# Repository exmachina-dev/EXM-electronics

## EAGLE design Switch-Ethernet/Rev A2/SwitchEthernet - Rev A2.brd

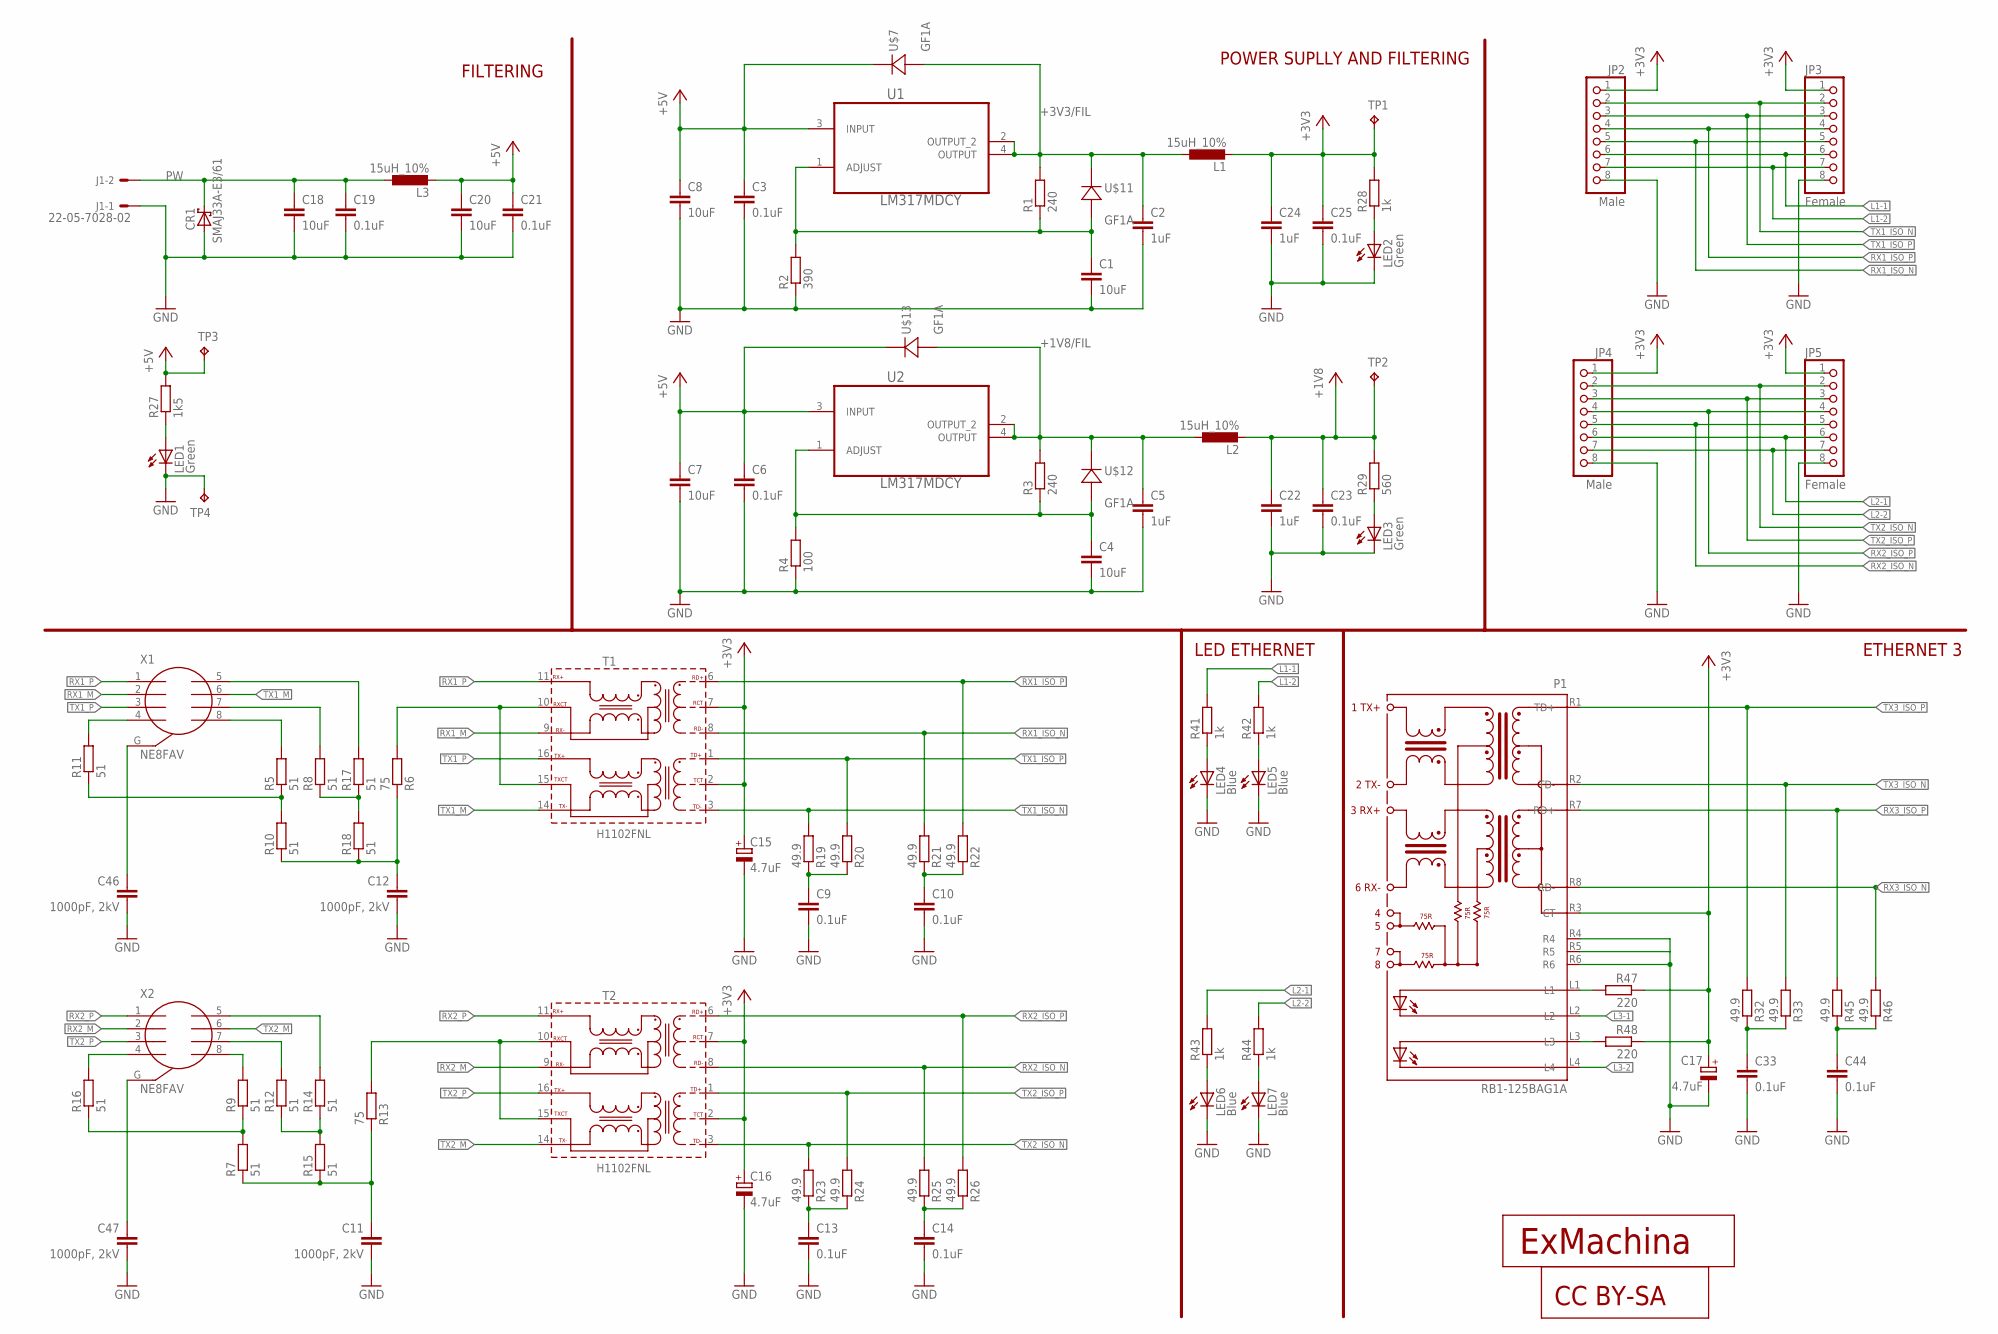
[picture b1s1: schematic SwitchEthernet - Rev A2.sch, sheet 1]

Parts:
C1, C4, C7, C8, C18, C20: 10uF; C0603; MPN MCNP16V106M5X11
C2, C5, C22, C24: 1uF; C0603; MPN MC0603B105K160CT
C3, C6, C9, C10, C13, C14, C19, C21, C23, C25, C33, C44: 0.1uF; C0603; MPN MC0603B104K160CT
C11, C12, C46, C47: 1000pF, 2kV; C1206; MPN MC1206B102K202CT
C15, C16, C17: 4.7uF; CT3216; MPN MCCTA475M010
CR1: SMAJ33A-E3/61; DIODE_DO-214AC; MPN SMAJ33A-E3/61
J1: 22-05-7028-02; 7395-02; MPN 22-05-7028
JP2, JP4: Male; 1X08; MPN 2211S-08G
JP3, JP5: Female; 1X08; MPN 2212S-08SG-85
L1, L2, L3: 15uH_10%; L4532M; MPN LQH43CN150K03L
LED1, LED2, LED3: Green; CHIP-LED0603; MPN OVS-0604
LED4, LED5, LED6, LED7: Blue; CHIP-LED0603; MPN OVS-0603
P1: RB1-125BAG1A; WIZNET_RB1-125BAG1A
R1, R3: 240; R0603; MPN MC0063W06031240R
R2: 390; R0603; MPN MC0063W06031390R
R4: 100; R0603; MPN MC0063W06031100R
R5, R7, R8, R9, R10, R11, R12, R14, R15, R16, R17, R18: 51; R0603; MPN MC0063W0603151R
R6, R13: 75; R0603; MPN MC0063W0603175R
R19, R20, R21, R22, R23, R24, R25, R26, R32, R33, R45, R46: 49.9; R0603; MPN MC0603SAF499JT5E
R27: 1k5; R0603; MPN MC0063W060311K5
R28, R41, R42, R43, R44: 1k; R0603; MPN MCMR06X1001FTL
R29: 560; R0603; MPN MCMR06X1501FTL
R47, R48: 220; R0603; MPN MC0063W06031220R
T1, T2: H1102FNL; HXXXX
TP1, TP2, TP3, TP4: TPB1,27; B1,27
U1, U2: LM317MDCY; SOT230P700X180-4N
U$5: EXMACHINA-LOGO-NAME; EXM-LOGO-BASELINE
U$6: CC-BY-SA
U$7, U$11, U$12, U$13: GF1A; DO-214BA; MPN GF1B-E3/67A
X1, X2: NE8FAV

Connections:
+1V8: C22.1, C23.1, L2.2, R29.2, TP2.TP; also elsewhere on the board
+1V8/FIL: C5.1, L2.1, R3.2, U2.2 (OUTPUT_2), U2.4 (OUTPUT), U$12.C (1), U$13.A (2)
+3V3: C15.+, C16.+, C17.+, C24.1, C25.1, JP2.1, JP3.1, JP4.1, JP5.1, L1.2, P1.R3 (CT), R28.2, R47.1, R48.1, T1.2 (TCT), T1.7 (RCT), T2.2 (TCT), T2.7 (RCT), TP1.TP; also elsewhere on the board
+3V3/FIL: C2.1, L1.1, R1.2, U1.2 (OUTPUT_2), U1.4 (OUTPUT), U$7.A (2), U$11.C (1)
+5V: C3.1, C6.1, C7.1, C8.1, C20.1, C21.1, L3.2, R27.2, TP3.TP, U1.3 (INPUT), U2.3 (INPUT), U$7.C (1), U$13.C (1)
GND: C1.2, C2.2, C3.2, C4.2, C5.2, C6.2, C7.2, C8.2, C9.2, C10.2, C11.2, C12.2, C13.2, C14.2, C15.-, C16.-, C17.-, C18.2, C19.2, C20.2, C21.2, C22.2, C23.2, C24.2, C25.2, C33.2, C44.2, C46.2, C47.2, CR1.2 (A), J1.1, JP2.8, JP3.8, JP4.8, JP5.8, LED1.C, LED2.C, LED3.C, LED4.C, LED5.C, LED6.C, LED7.C, P1.R4, P1.R5, P1.R6, R2.1, R4.1, TP4.TP; also elsewhere on the board
L1-1: JP2.6, JP3.6, R41.2; also elsewhere on the board
L1-2: JP2.7, JP3.7, R42.2; also elsewhere on the board
L2-1: JP4.6, JP5.6, R43.2; also elsewhere on the board
L2-2: JP4.7, JP5.7, R44.2; also elsewhere on the board
L3-1: P1.L2; also elsewhere on the board
L3-2: P1.L4; also elsewhere on the board
unnamed: R6.2, T1.10 (RXCT), T1.15 (TXCT)
unnamed: C1.1, R1.1, R2.2, U1.1 (ADJUST), U$11.A (2)
unnamed: R13.2, T2.10 (RXCT), T2.15 (TXCT)
unnamed: R9.2, X2.8
unnamed: C4.1, R3.1, R4.2, U2.1 (ADJUST), U$12.A (2)
unnamed: R11.2, X1.4
unnamed: R5.2, X1.8
unnamed: R8.2, X1.7
unnamed: C9.1, R19.1, R20.1
unnamed: R17.2, X1.5
unnamed: R12.2, X2.7
unnamed: C11.1, R7.1, R13.1, R15.1
unnamed: R5.1, R10.2, R11.1
unnamed: R16.2, X2.4
unnamed: R7.2, R9.1, R16.1
unnamed: R8.1, R17.1, R18.2
unnamed: R14.2, X2.5
unnamed: R12.1, R14.1, R15.2
unnamed: LED4.A, R41.1
unnamed: LED1.A, R27.1
unnamed: LED2.A, R28.1
unnamed: LED3.A, R29.1
unnamed: C33.1, R32.1, R33.1
unnamed: LED5.A, R42.1
unnamed: LED6.A, R43.1
unnamed: LED7.A, R44.1
unnamed: C44.1, R45.1, R46.1
unnamed: C12.1, R6.1, R10.1, R18.1
unnamed: C10.1, R21.1, R22.1
unnamed: P1.L3, R48.2
unnamed: P1.L1, R47.2
unnamed: C47.1, X2.G
unnamed: C46.1, X1.G
unnamed: C13.1, R23.1, R24.1
unnamed: C14.1, R25.1, R26.1
PW: C18.1, C19.1, CR1.1 (C), J1.2, L3.1
RX1_ISO_N: JP2.5, JP3.5, R21.2, T1.8 (RD-); also elsewhere on the board
RX1_ISO_P: JP2.4, JP3.4, R22.2, T1.6 (RD+); also elsewhere on the board
RX1_M: T1.9 (RX-), X1.2
RX1_P: T1.11 (RX+), X1.1
RX2_ISO_N: JP4.5, JP5.5, R25.2, T2.8 (RD-); also elsewhere on the board
RX2_ISO_P: JP4.4, JP5.4, R26.2, T2.6 (RD+); also elsewhere on the board
RX2_M: T2.9 (RX-), X2.2
RX2_P: T2.11 (RX+), X2.1
RX3_ISO_N: P1.R8 (RD-), R46.2; also elsewhere on the board
RX3_ISO_P: P1.R7 (RD+), R45.2; also elsewhere on the board
TX1_ISO_N: JP2.2, JP3.2, R19.2, T1.3 (TD-); also elsewhere on the board
TX1_ISO_P: JP2.3, JP3.3, R20.2, T1.1 (TD+); also elsewhere on the board
TX1_M: T1.14 (TX-), X1.6
TX1_P: T1.16 (TX+), X1.3
TX2_ISO_N: JP4.2, JP5.2, R23.2, T2.3 (TD-); also elsewhere on the board
TX2_ISO_P: JP4.3, JP5.3, R24.2, T2.1 (TD+); also elsewhere on the board
TX2_M: T2.14 (TX-), X2.6
TX2_P: T2.16 (TX+), X2.3
TX3_ISO_N: P1.R2 (TD-), R33.2; also elsewhere on the board
TX3_ISO_P: P1.R1 (TD+), R32.2; also elsewhere on the board

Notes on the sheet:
FILTERING
POWER SUPLLY AND FILTERING
LED ETHERNET
ETHERNET 3

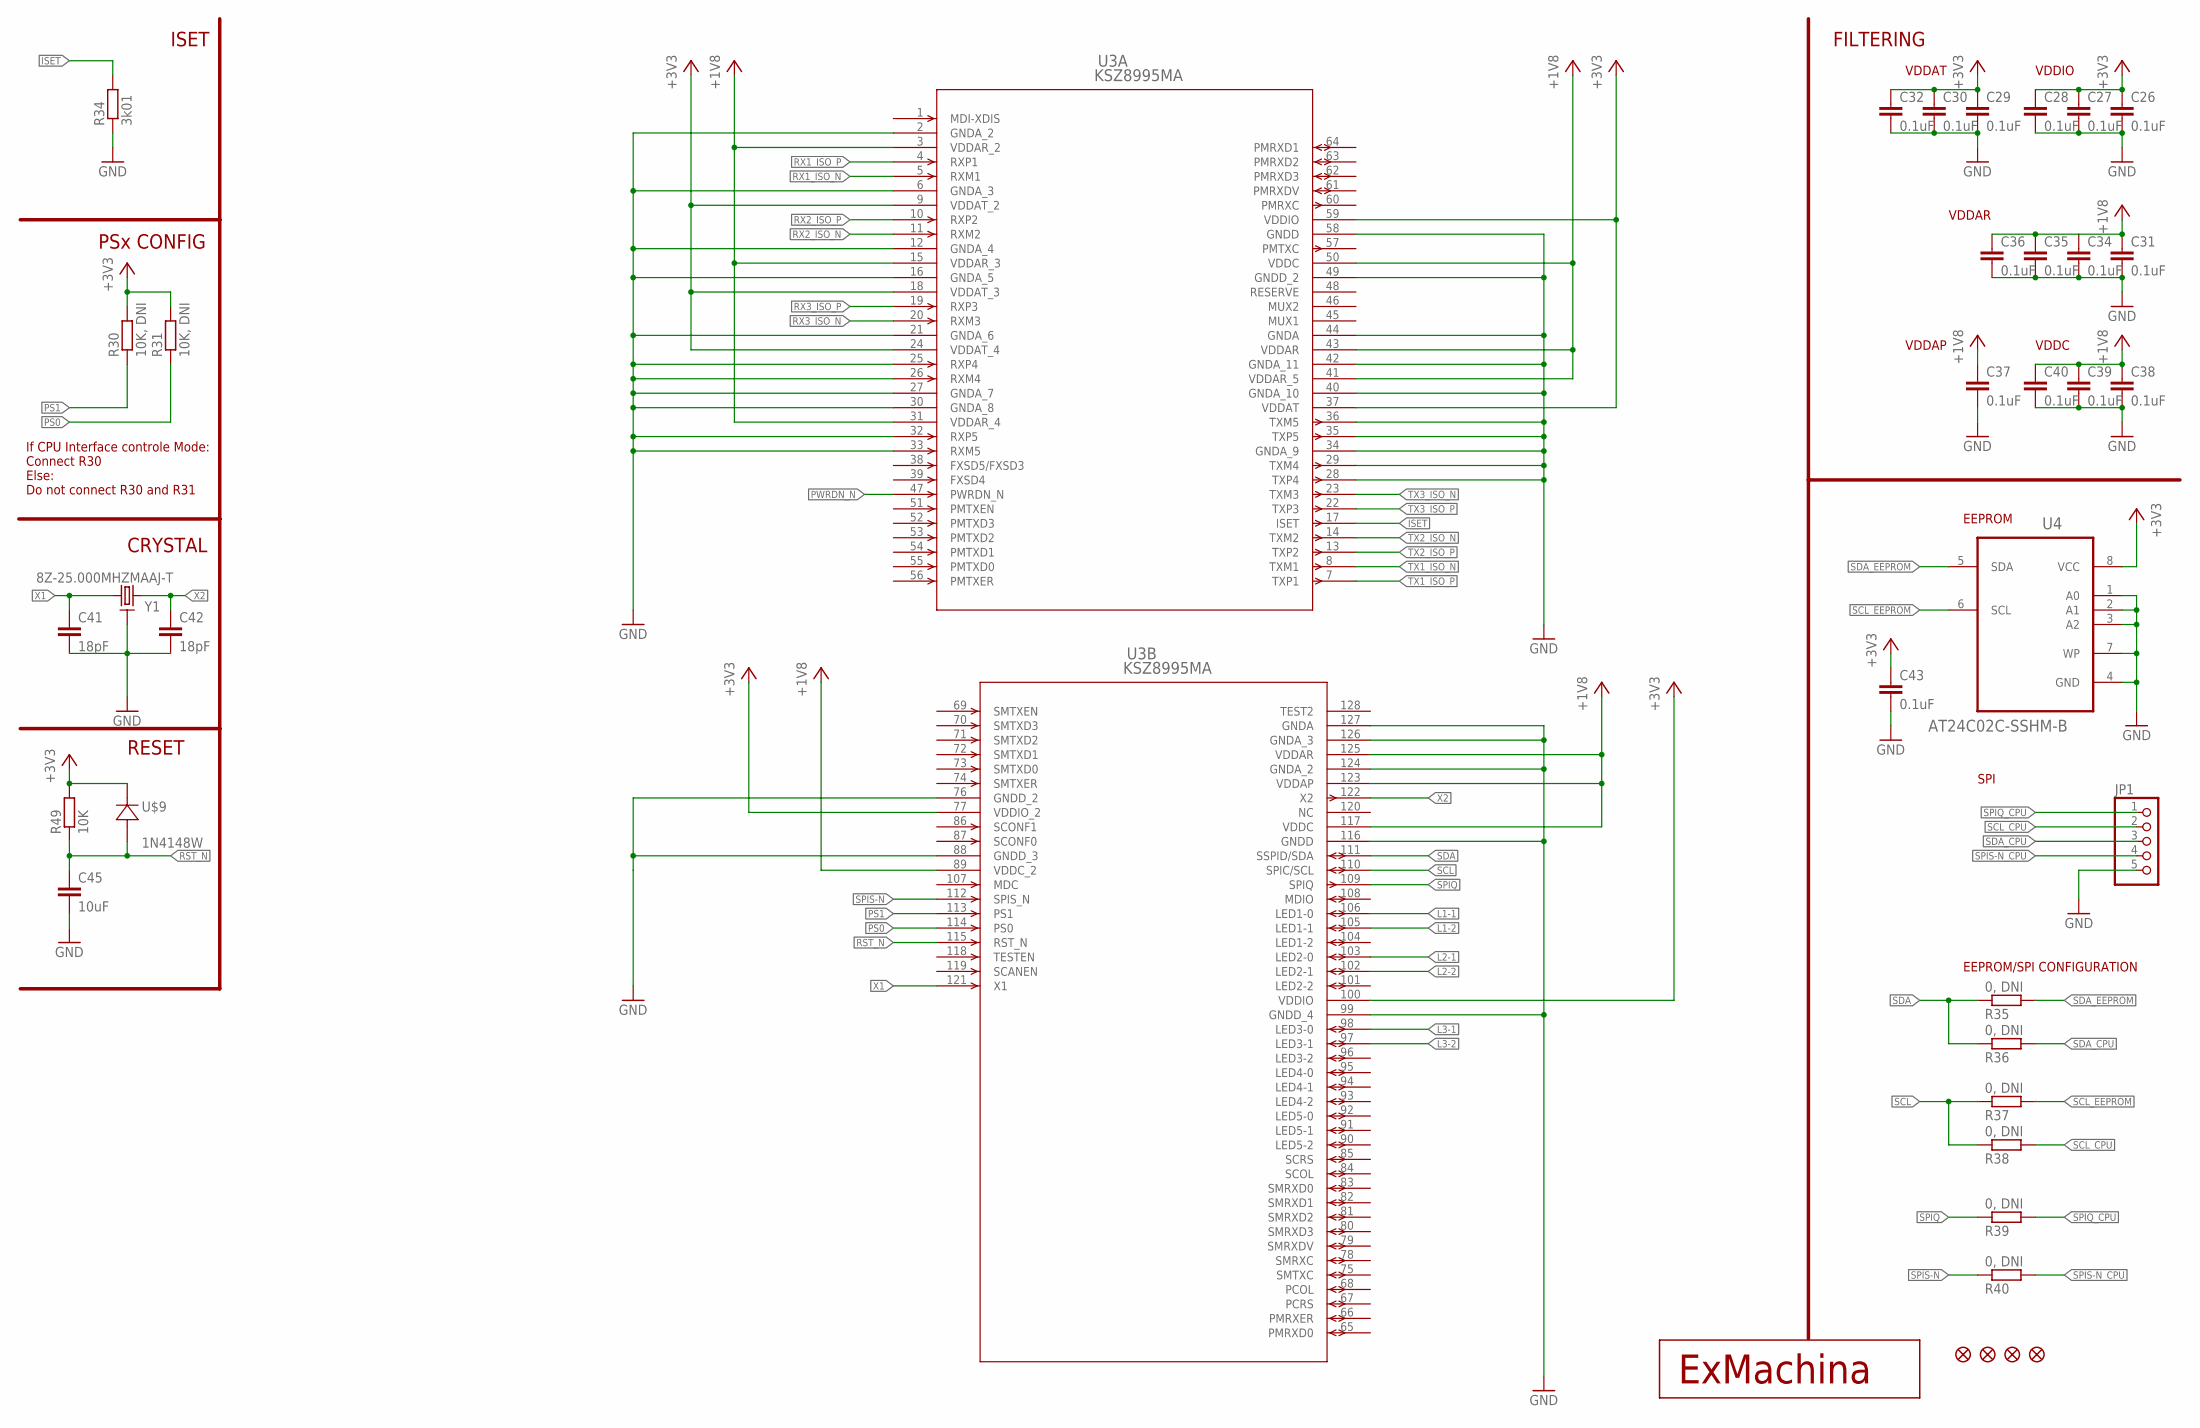
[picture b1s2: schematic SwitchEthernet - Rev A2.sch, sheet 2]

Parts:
C26, C27, C28, C29, C30, C31, C32, C34, C35, C36, C37, C38, C39, C40, C43: 0.1uF; C0603; MPN MC0603B104K160CT
C41, C42: 18pF; C0603; MPN MC0603N180J500CT
C45: 10uF; C0603; MPN MCNP16V106M5X11
JP1: PINHD-1X5; 1X05; MPN M20-9990545
JP7, JP8, JP9, JP10: FIDUCIAL1X2; FIDUCIAL-1X2
R30, R31: 10K, DNI; R0603; MPN MC0063W0603110K
R34: 3k01; R0603; MPN MC0063W060313K01
R35, R36, R37, R38, R39, R40: 0, DNI; R0603; MPN MC0603WG00000T5E-TC
R49: 10K; R0603; MPN MC0063W0603110K
U3: KSZ8995MA; PQFP-128_MQL; MPN KSZ8995MA
U4: AT24C02C-SSHM-B; SOIC127P600X175-8N
U$8: EXMACHINA-LOGO-NAME; EXM-LOGO-BASELINE
U$9: 1N4148W; SOD-123_MINI-SMA; MPN 1N4148W
Y1: 8Z-25.000MHZMAAJ-T; SMD2.5X2; MPN 8Z-25.000MAAJ-T

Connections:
+1V8: C31.1, C34.1, C35.1, C36.1, C37.1, C38.1, C39.1, C40.1, U3.3 (VDDAR_2), U3.15 (VDDAR_3), U3.31 (VDDAR_4), U3.41 (VDDAR_5), U3.43 (VDDAR), U3.50 (VDDC), U3.89 (VDDC_2), U3.117 (VDDC), U3.123 (VDDAP), U3.125 (VDDAR); also elsewhere on the board
+3V3: C26.1, C27.1, C28.1, C29.1, C30.1, C32.1, C43.1, R30.2, R31.2, R49.2, U3.9 (VDDAT_2), U3.18 (VDDAT_3), U3.24 (VDDAT_4), U3.37 (VDDAT), U3.59 (VDDIO), U3.77 (VDDIO_2), U3.100 (VDDIO), U4.8 (VCC), U$9.C (1); also elsewhere on the board
GND: C26.2, C27.2, C28.2, C29.2, C30.2, C31.2, C32.2, C34.2, C35.2, C36.2, C37.2, C38.2, C39.2, C40.2, C41.2, C42.2, C43.2, C45.2, JP1.5, R34.1, U3.2 (GNDA_2), U3.6 (GNDA_3), U3.12 (GNDA_4), U3.16 (GNDA_5), U3.21 (GNDA_6), U3.25 (RXP4), U3.26 (RXM4), U3.27 (GNDA_7), U3.28 (TXP4), U3.29 (TXM4), U3.30 (GNDA_8), U3.32 (RXP5), U3.33 (RXM5), U3.34 (GNDA_9), U3.35 (TXP5), U3.36 (TXM5), U3.40 (GNDA_10), U3.42 (GNDA_11), U3.44 (GNDA), U3.49 (GNDD_2), U3.58 (GNDD), U3.76 (GNDD_2), U3.88 (GNDD_3), U3.99 (GNDD_4), U3.116 (GNDD), U3.124 (GNDA_2), U3.126 (GNDA_3), U3.127 (GNDA), U4.1 (A0), U4.2 (A1), U4.3 (A2), U4.4 (GND), U4.7 (WP), Y1.2, Y1.4 (2); also elsewhere on the board
ISET: R34.2, U3.17 (ISET)
L1-1: U3.106 (LED1-0); also elsewhere on the board
L1-2: U3.105 (LED1-1); also elsewhere on the board
L2-1: U3.103 (LED2-0); also elsewhere on the board
L2-2: U3.102 (LED2-1); also elsewhere on the board
L3-1: U3.98 (LED3-0); also elsewhere on the board
L3-2: U3.97 (LED3-1); also elsewhere on the board
PS0: R31.1, U3.114 (PS0)
PS1: R30.1, U3.113 (PS1)
PWRDN_N: U3.47 (PWRDN_N)
RST_N: C45.1, R49.1, U3.115 (RST_N), U$9.A (2)
RX1_ISO_N: U3.5 (RXM1); also elsewhere on the board
RX1_ISO_P: U3.4 (RXP1); also elsewhere on the board
RX2_ISO_N: U3.11 (RXM2); also elsewhere on the board
RX2_ISO_P: U3.10 (RXP2); also elsewhere on the board
RX3_ISO_N: U3.20 (RXM3); also elsewhere on the board
RX3_ISO_P: U3.19 (RXP3); also elsewhere on the board
SCL: R37.1, R38.1, U3.110 (SPIC/SCL)
SCL_CPU: JP1.2, R38.2
SCL_EEPROM: R37.2, U4.6 (SCL)
SDA: R35.1, R36.1, U3.111 (SSPID/SDA)
SDA_CPU: JP1.3, R36.2
SDA_EEPROM: R35.2, U4.5 (SDA)
SPIQ: R39.1, U3.109 (SPIQ)
SPIQ_CPU: JP1.1, R39.2
SPIS-N: R40.1, U3.112 (SPIS_N)
SPIS-N_CPU: JP1.4, R40.2
TX1_ISO_N: U3.8 (TXM1); also elsewhere on the board
TX1_ISO_P: U3.7 (TXP1); also elsewhere on the board
TX2_ISO_N: U3.14 (TXM2); also elsewhere on the board
TX2_ISO_P: U3.13 (TXP2); also elsewhere on the board
TX3_ISO_N: U3.23 (TXM3); also elsewhere on the board
TX3_ISO_P: U3.22 (TXP3); also elsewhere on the board
X1: C41.1, U3.121 (X1), Y1.1
X2: C42.1, U3.122 (X2), Y1.3

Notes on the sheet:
ISET
FILTERING
VDDIO
VDDAT
VDDAR
VDDC
VDDAP
PSx CONFIG
If CPU Interface controle Mode: Connect R30 Else: Do not connect R30 and R31
CRYSTAL
EEPROM
SPI
EEPROM/SPI CONFIGURATION
RESET

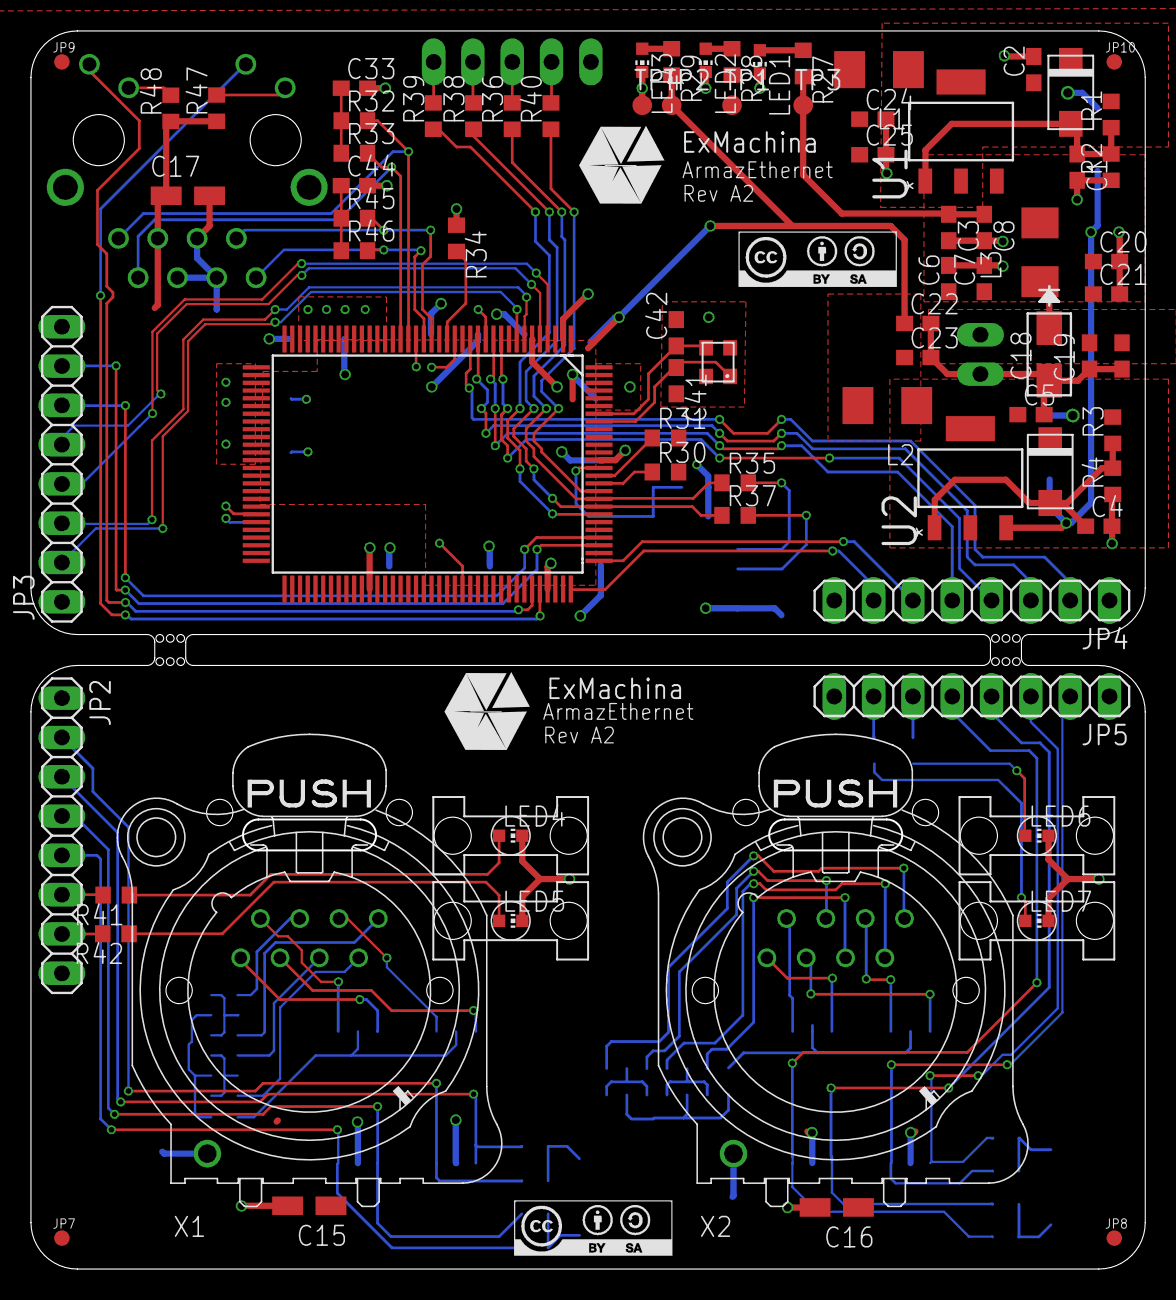
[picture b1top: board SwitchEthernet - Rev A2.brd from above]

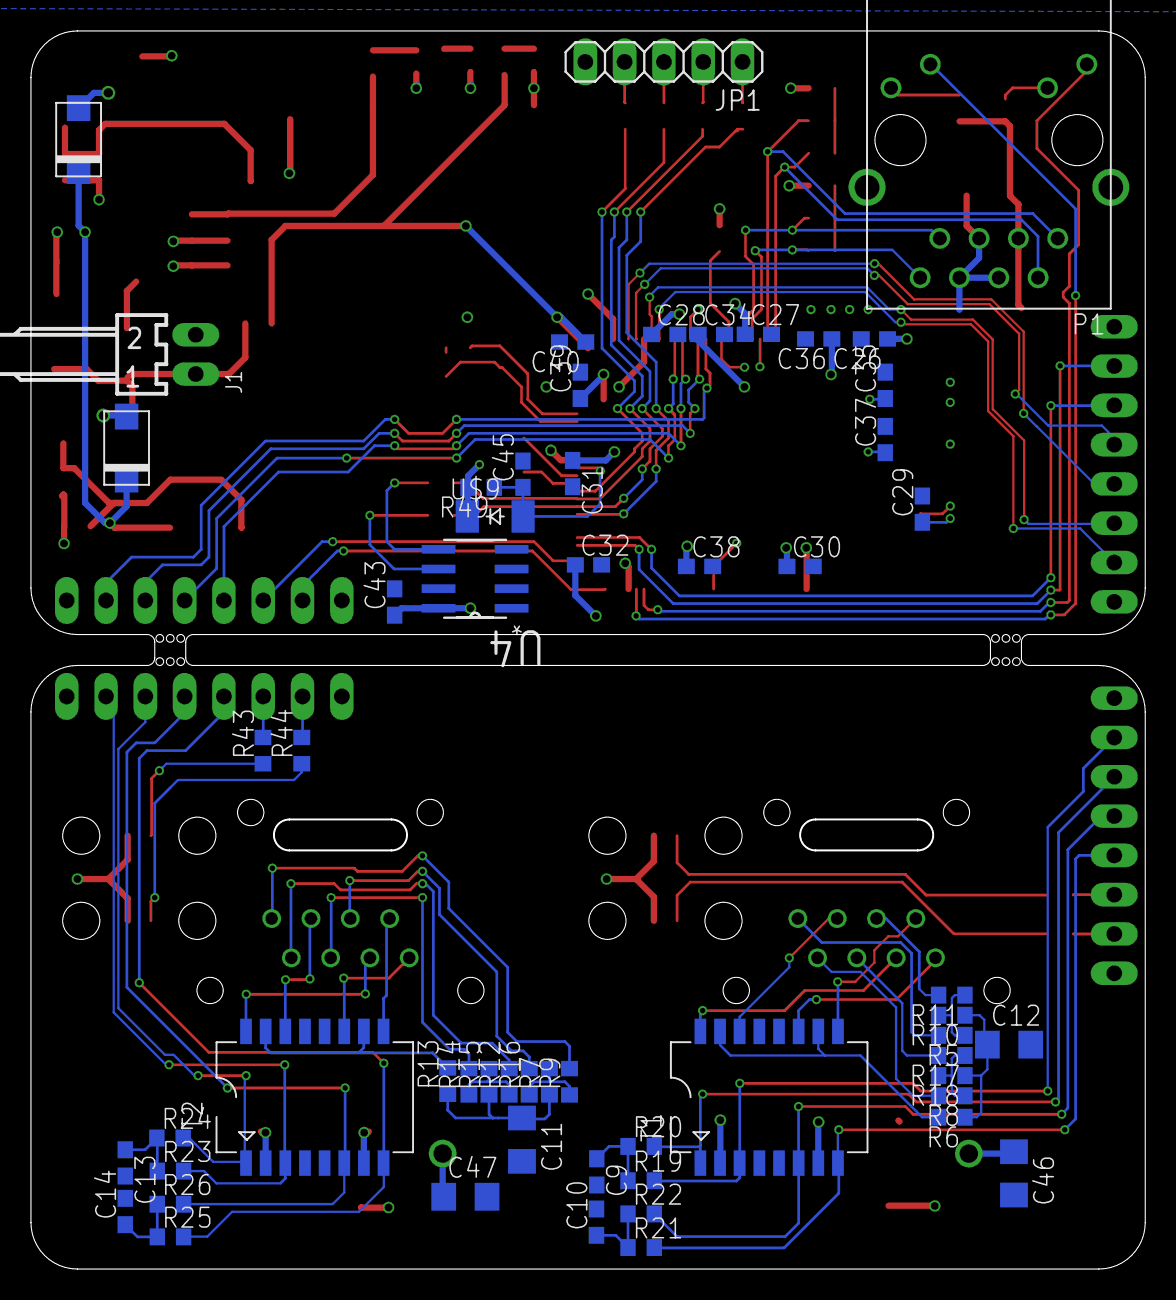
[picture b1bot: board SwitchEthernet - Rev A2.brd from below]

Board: 2 copper layers, 72.0 x 80.0 mm, 144 parts (58 on the bottom side), 84 nets.

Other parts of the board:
U$1, U$2, U$3, U$4: 1275.100
U$10: CC-BY-SA

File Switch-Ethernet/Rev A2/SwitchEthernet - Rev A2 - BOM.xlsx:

Qty | Value | Device | Package | Parts | Description COPYRIGHT | FAMILY MANUFACTURER_NAME MANUFACTURER_PART_NUMBER MF | MPN OC_FARNELL | OC_NEWARK PACKAGE RSPARTNUMBER SECTION SUPERSECTION SUPPLIER TP_SIGNAL_NAME VEN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
1 |  | PINHD-1X5 | 1X05 | JP1 | PIN HEADER |  | M20-9990545 | 97K6210
6 | 0, DNI | R-EU_R0603 | R0603 | R35, R36, R37, R38, R39, R40 | RESISTOR, European symbol | Multicomp | MC0603WG00000T5E-TC | 58K4684
27 | 0.1uF | C-EUC0603 | C0603 | C3, C6, C9, C10, C13, C14, C19, C21, C23, C25, C26, C27, C28, C29, C30, C31, C3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 | CAPACITOR, European symbol |  | MC0603B104K160CT | 06R4923
1 | 100 | R-EU_R0603 | R0603 | R4 | RESISTOR, European symbol | Multicomp | MC0063W06031100R | 58K4446
4 | 1000pF, 2kV | C-EUC1206 | C1206 | C11, C12, C46, C47 | CAPACITOR, European symbol |  | MC1206B102K202CT | 21T9879
1 | 10K | R-EU_R0603 | R0603 | R49 | RESISTOR, European symbol | Multicomp | MC0063W0603110K | 58K4450
2 | 10K, DNI | R-EU_R0603 | R0603 | R30, R31 | RESISTOR, European symbol | Multicomp | MC0063W0603110K | 58K4450
7 | 10uF | C-EUC0603 | C0603 | C1, C4, C7, C8, C18, C20, C45 | CAPACITOR, European symbol |  | MCNP16V106M5X11 | 13M5149
3 | 15uH_10% | L-EUL4532C | L4532M | L1, L2, L3 | INDUCTOR, European symbol |  | LQH43CN150K03L | 74M2809
2 | 18pF | C-EUC0603 | C0603 | C41, C42 | CAPACITOR, European symbol |  | MC0603N180J500CT | 06R5138
1 | 1N4148W | 1N4148W | SOD-123_MINI-SMA | U$9 |  |  | 1N4148W | 01P4213
5 | 1k | R-EU_R0603 | R0603 | R28, R41, R42, R43, R44 | RESISTOR, European symbol |  | MCMR06X1001FTL | 86T3505
1 | 1k5 | R-EU_R0603 | R0603 | R27 | RESISTOR, European symbol | Multicomp | MC0063W060311K5 | 58K4488
4 | 1uF | C-EUC0603 | C0603 | C2, C5, C22, C24 | CAPACITOR, European symbol |  | MC0603B105K160CT | 06X6171
1 | 22-05-7028-02 | 22-05-7028-02 | 2007041 | J1 | CONNECTOR |  | 22-05-7028 9731601 | 25M1728
2 | 220 | R-EU_R0603 | R0603 | R47, R48 | RESISTOR, European symbol | Multicomp | MC0063W06031220R | 58K4526
2 | 240 | R-EU_R0603 | R0603 | R1, R3 | RESISTOR, European symbol |  | MC0063W06031240R | 94W5763
1 | 390 | R-EU_R0603 | R0603 | R2 | RESISTOR, European symbol | Multicomp | MC0063W06031390R | 58K4586
1 | 3k01 | R-EU_R0603 | R0603 | R34 | RESISTOR, European symbol |  | MC0063W060313K01 | 94W5780
3 | 4.7uF | CPOL-EUCT3216 | CT3216 | C15, C16, C17 | POLARIZED CAPACITOR, European symbol |  | MCCTA475M010 | 01M8221
12 | 49.9 | R-EU_R0603 | R0603 | R19, R20, R21, R22, R23, R24, R25, R26, R32, R33, R45, R46 | RESISTOR, European symbol |  | MC0603SAF499JT5E | 79M5983
12 | 51 | R-EU_R0603 | R0603 | R5, R7, R8, R9, R10, R11, R12, R14, R15, R16, R17, R18 | RESISTOR, European symbol | Multicomp | MC0063W0603151R | 58K4614
1 | 560 | R-EU_R0603 | R0603 | R29 | RESISTOR, European symbol |  | MCMR06X1501FTL | 86T3542
2 | 75 | R-EU_R0603 | R0603 | R6, R13 | RESISTOR, European symbol | Multicomp | MC0063W0603175R | 58K4654
1 | 8Z-25.000MHZM | AAJ-T 8Z-25.000MHZMAAJ-T | SMD2.5X2 | Y1 |  |  | 8Z-25.000MAAJ-T | 84R5794
1 | AT24C02C-SSHM | #NAME? | SOIC127P600X175-8N | U4 | SERIAL EEPROM IC Memory Size:2Kbit,8-SOIC |  | AT24C02C-SSHM-B 1971995 | 68T4066 8SOIC ATMEL
4 | Blue | LEDCHIP-LED0603 | CHIP-LED0603 | LED4, LED5, LED6, LED7 | LED |  | OVS-0603 | 15R2205
1 | CC-BY-SA | CC-BY-SA | CC-BY-SA | U$6 |  |  |  | unknown
2 | EXMACHINA-LOG | O-NAME EXMACHINA-LOGO-NAME | EXM-LOGO-BASELINE | U$5, U$8 |  |  |  | unknown
2 | Female | PINHD-1X8 | 1X08 | JP3, JP5 | PIN HEADER |  | 2212S-08SG-85 | 08N6773
4 | GF1A | GF1A | DO-214BA | U$7, U$11, U$12, U$13 |  |  | GF1B-E3/67A | 05R5601
3 | Green | LEDCHIP-LED0603 | CHIP-LED0603 | LED1, LED2, LED3 | LED |  | OVS-0604 | 15R2206
2 | H1102FNL | H1102FNL | HXXXX | T1, T2 |  |  |  | unknown
1 | KSZ8995MA | KSZ8995MA | PQFP-128_MQL | U3 | Copyright (C) 2015 Accelerated Des | igns. All rights reserved ksz8995ma | KSZ8995MA | 70Y9044 MICREL
2 | LM317MDCY | LM317MDCY | SOT230P700X180-4N | U1, U2 | IC ADJ LINEAR REG 1.25V TO 37V | TEXAS INS | LM317MDCY 1648658 | 75C0818 SOT-223-3 TEXAS INSTRUMENTS
2 | Male | PINHD-1X8 | 1X08 | JP2, JP4 | PIN HEADER |  | 2211S-08G | 08N6749
2 | NE8FAV | NE8FAV | NE8FAV | X1, X2 |  |  | NE8FAV unknown | 01M8373
1 | RB1-125BAG1A | RB1-125BAG1A | WIZNET_RB1-125BAG1A | P1 | Accessory RJ-45 With Transformer Connector - UDE |  |  | unknown
1 | SMAJ33A-E3/61 | SMAJ33A-E3/61 | DIODE_DO-214AC | CR1 | Copyright (C) 2015 Accelerated Des | igns. All rights reserved TVS Vishay SMAJ33A-E3/61 | SMAJ33A-E3/61 | 08R3790 7103462 Discretes Semiconductors Vishay
4 | TPB1,27 | TPB1,27 | B1,27 | TP1, TP2, TP3, TP4 | Test pad |  |  | unknown

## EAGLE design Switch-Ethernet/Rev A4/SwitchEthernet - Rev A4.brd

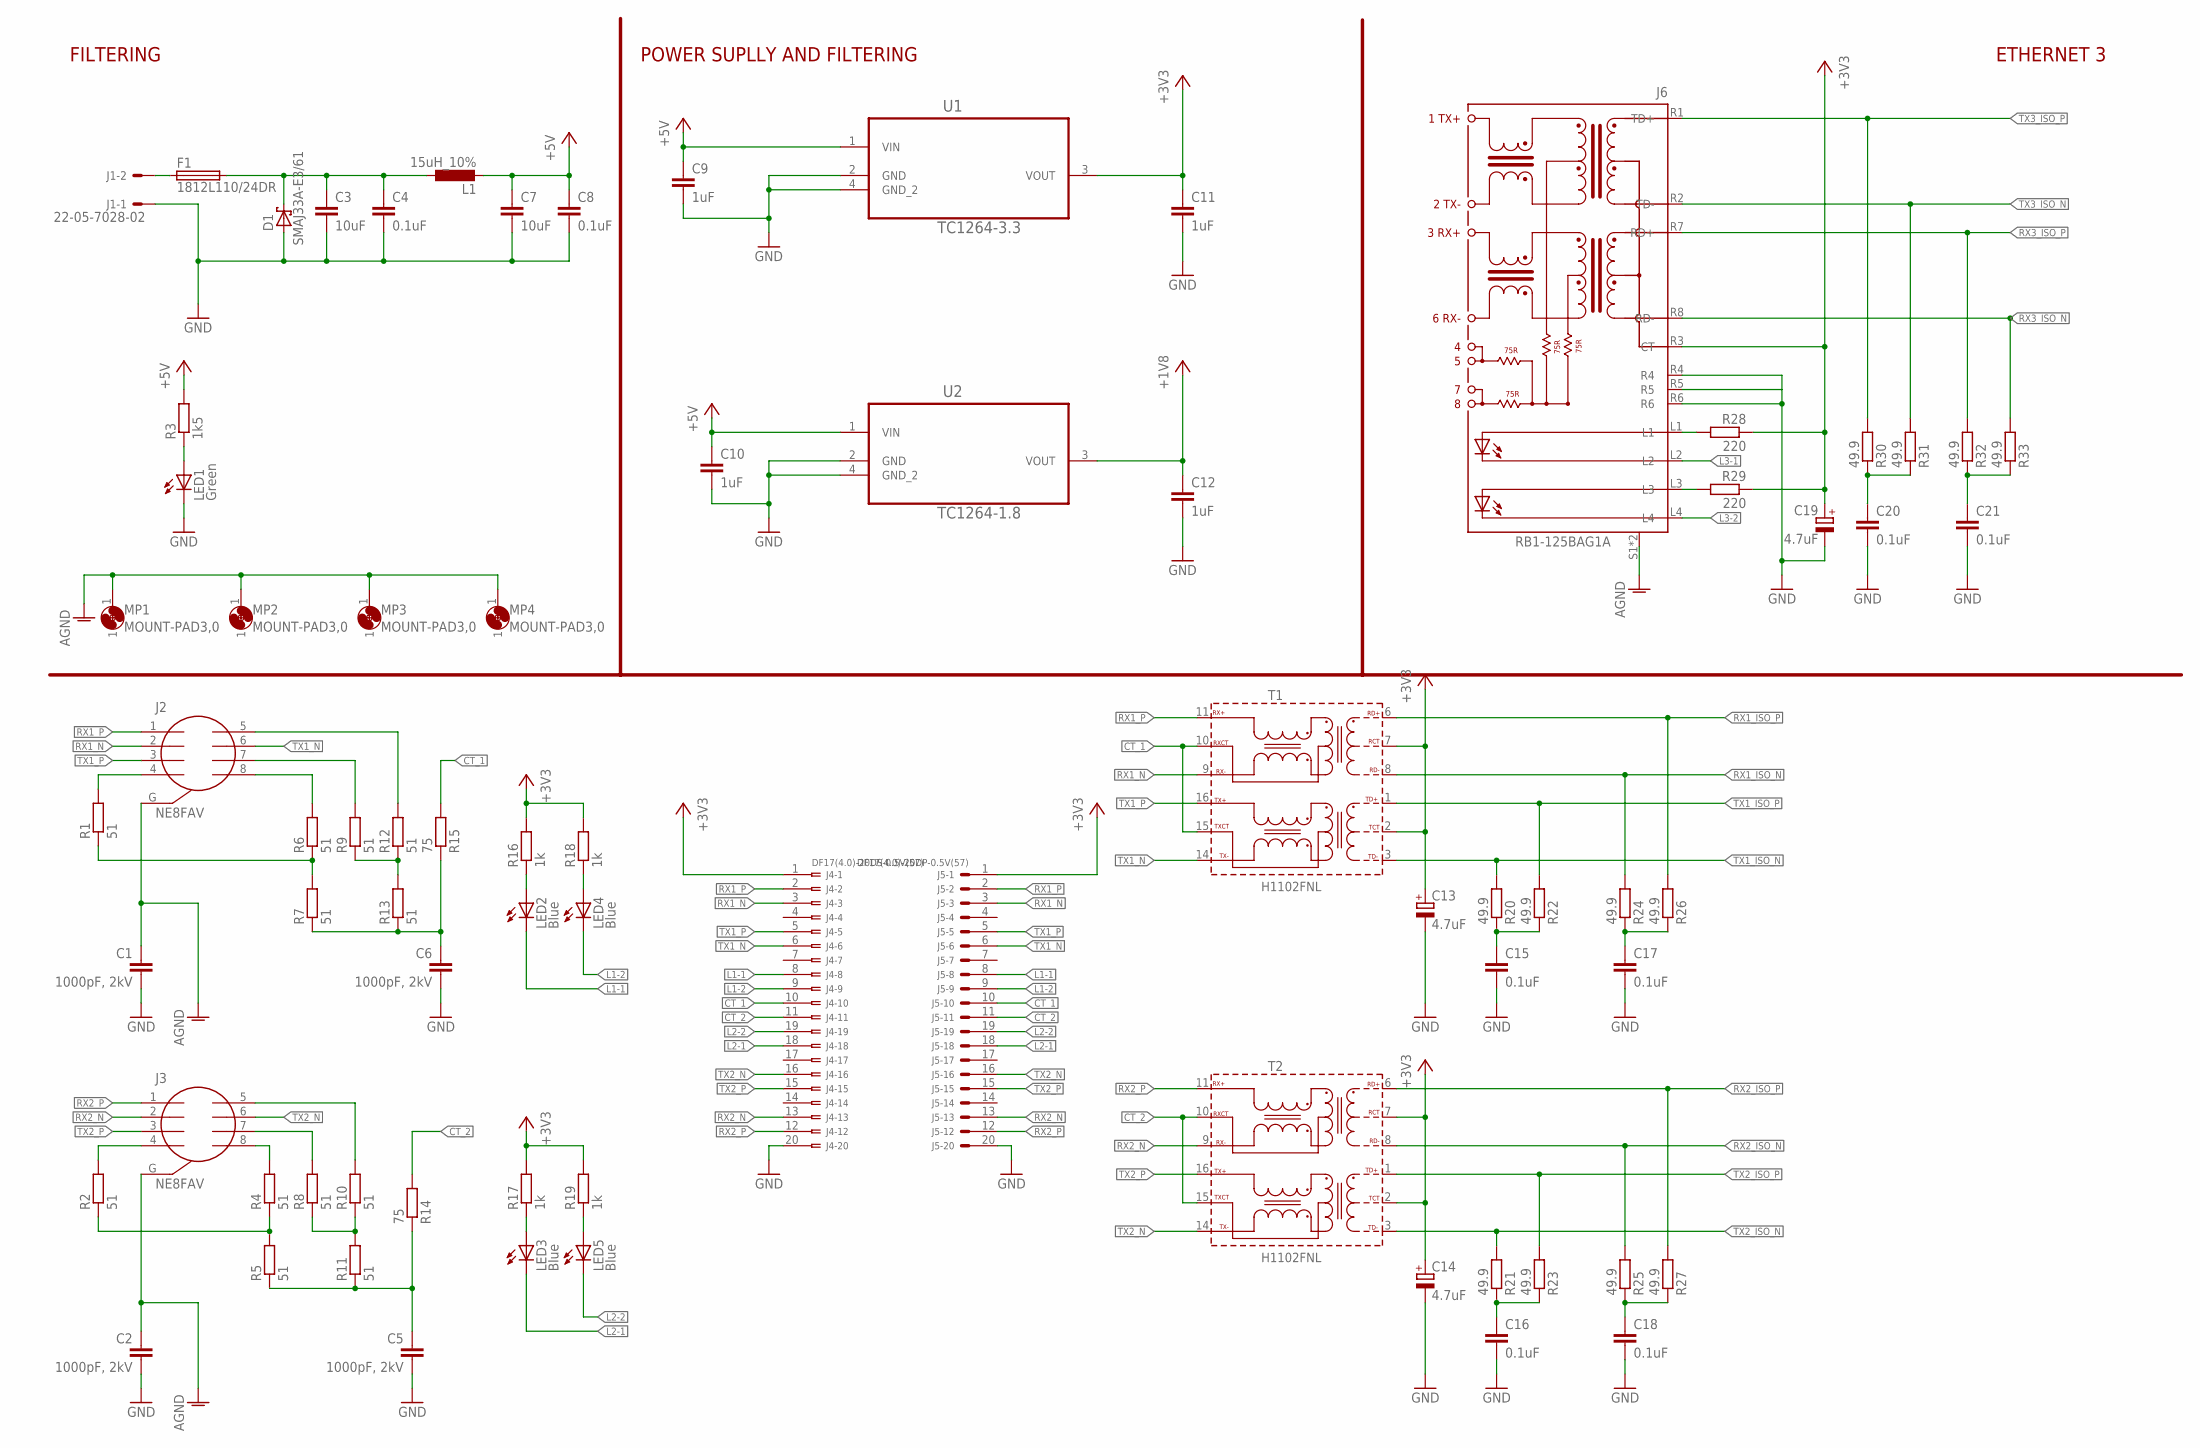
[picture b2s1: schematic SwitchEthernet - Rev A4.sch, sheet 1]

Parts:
C1, C2, C5, C6: 1000pF, 2kV; C1206; MPN MC1206B102K202CT
C3, C7: 10uF; C0603; MPN GRM188R60J106ME47D
C4, C8, C15, C16, C17, C18, C20, C21: 0.1uF; C0603; MPN MC0603B104K160CT
C9, C10, C11, C12: 1uF; C0603; MPN MC0603B105K160CT
C13, C14, C19: 4.7uF; CT3216; MPN MCCTA475M010
D1: SMAJ33A-E3/61; DIODE_DO-214AC
F1: 1812L110/24DR; LITTLEFUSE_SMD; MPN 1812L110/24DR
J1: 22-05-7028-02; 7395-02; MPN 22-05-7028
J2, J3: NE8FAV
J4: DF17(4.0)-20DS-0.5V(57); DF17-20DS; MPN DF17(4.0)-20DS-0.5V(57)
J5: DF17(4.0)-20DP-0.5V(57); DF17-20DP; MPN DF17(4.0)-20DP-0.5V(57)
J6: RB1-125BAG1A; WIZNET_RB1-125BAG1A
L1: 15uH_10%; L4532M; MPN LQH43CN150K03L
LED1: Green; CHIP-LED0603; MPN OVS-0604
LED2, LED3, LED4, LED5: Blue; CHIP-LED0603; MPN OVS-0603
MP1, MP2, MP3, MP4: MOUNT-PAD3,0; P3,0
R1, R2, R4, R5, R6, R7, R8, R9, R10, R11, R12, R13: 51; R0603; MPN MC0063W0603151R
R3: 1k5; R0603; MPN MC0063W060311K5
R14, R15: 75; R0603; MPN MC0063W0603175R
R16, R17, R18, R19: 1k; R0603; MPN MCMR06X1001FTL
R20, R21, R22, R23, R24, R25, R26, R27, R30, R31, R32, R33: 49.9; R0603; MPN MC0603SAF499JT5E
R28, R29: 220; R0603; MPN MC0063W06031220R
T1, T2: H1102FNL; HXXXX
U1: TC1264-3.3; SOT230P700X180-4N; MPN TC1264-3.3VDB
U2: TC1264-1.8; SOT230P700X180-4N; MPN TC1264-1.8VDBTR

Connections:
+1V8: C12.1, U2.3 (VOUT); also elsewhere on the board
+3V3: C11.1, C13.+, C14.+, C19.+, J4.1, J5.1, J6.R3 (CT), R16.2, R17.2, R18.2, R19.2, R28.1, R29.1, T1.2 (TCT), T1.7 (RCT), T2.2 (TCT), T2.7 (RCT), U1.3 (VOUT); also elsewhere on the board
+5V: C7.1, C8.1, C9.1, C10.1, L1.2, R3.2, U1.1 (VIN), U2.1 (VIN)
AGND: C1.1, C2.1, J2.G, J3.G, J6.S1, J6.S2, MP1.1, MP2.1, MP3.1, MP4.1
CT_1: J4.10, J5.10, R15.2, T1.10 (RXCT), T1.15 (TXCT)
CT_2: J4.11, J5.11, R14.2, T2.10 (RXCT), T2.15 (TXCT)
GND: C1.2, C2.2, C3.2, C4.2, C5.2, C6.2, C7.2, C8.2, C9.2, C10.2, C11.2, C12.2, C13.-, C14.-, C15.2, C16.2, C17.2, C18.2, C19.-, C20.2, C21.2, D1.2 (A), J1.1, J4.20, J5.20, J6.R4, J6.R5, J6.R6, LED1.C, U1.2 (GND), U1.4 (GND_2), U2.2 (GND), U2.4 (GND_2); also elsewhere on the board
L1-1: J4.8, J5.8, LED2.C; also elsewhere on the board
L1-2: J4.9, J5.9, LED4.C; also elsewhere on the board
L2-1: J4.18, J5.18, LED3.C; also elsewhere on the board
L2-2: J4.19, J5.19, LED5.C; also elsewhere on the board
L3-1: J6.L2; also elsewhere on the board
L3-2: J6.L4; also elsewhere on the board
unnamed: F1.1, J1.2
unnamed: J3.8, R4.2
unnamed: J2.4, R1.2
unnamed: J2.8, R6.2
unnamed: J2.7, R9.2
unnamed: C15.1, R20.1, R22.1
unnamed: J2.5, R12.2
unnamed: J3.7, R8.2
unnamed: C5.1, R5.1, R11.1, R14.1
unnamed: R1.1, R6.1, R7.2
unnamed: J3.4, R2.2
unnamed: R2.1, R4.1, R5.2
unnamed: R9.1, R12.1, R13.2
unnamed: J3.5, R10.2
unnamed: R8.1, R10.1, R11.2
unnamed: LED2.A, R16.1
unnamed: LED1.A, R3.1
unnamed: C20.1, R30.1, R31.1
unnamed: LED4.A, R18.1
unnamed: LED3.A, R17.1
unnamed: LED5.A, R19.1
unnamed: C21.1, R32.1, R33.1
unnamed: C6.1, R7.1, R13.1, R15.1
unnamed: C17.1, R24.1, R26.1
unnamed: J6.L3, R29.2
unnamed: J6.L1, R28.2
unnamed: C16.1, R21.1, R23.1
unnamed: C18.1, R25.1, R27.1
PW: C3.1, C4.1, D1.1 (C), F1.2, L1.1
RX1_ISO_N: R24.2, T1.8 (RD-); also elsewhere on the board
RX1_ISO_P: R26.2, T1.6 (RD+); also elsewhere on the board
RX1_N: J2.2, J4.3, J5.3, T1.9 (RX-)
RX1_P: J2.1, J4.2, J5.2, T1.11 (RX+)
RX2_ISO_N: R25.2, T2.8 (RD-); also elsewhere on the board
RX2_ISO_P: R27.2, T2.6 (RD+); also elsewhere on the board
RX2_N: J3.2, J4.13, J5.13, T2.9 (RX-)
RX2_P: J3.1, J4.12, J5.12, T2.11 (RX+)
RX3_ISO_N: J6.R8 (RD-), R33.2; also elsewhere on the board
RX3_ISO_P: J6.R7 (RD+), R32.2; also elsewhere on the board
TX1_ISO_N: R20.2, T1.3 (TD-); also elsewhere on the board
TX1_ISO_P: R22.2, T1.1 (TD+); also elsewhere on the board
TX1_N: J2.6, J4.6, J5.6, T1.14 (TX-)
TX1_P: J2.3, J4.5, J5.5, T1.16 (TX+)
TX2_ISO_N: R21.2, T2.3 (TD-); also elsewhere on the board
TX2_ISO_P: R23.2, T2.1 (TD+); also elsewhere on the board
TX2_N: J3.6, J4.16, J5.16, T2.14 (TX-)
TX2_P: J3.3, J4.15, J5.15, T2.16 (TX+)
TX3_ISO_N: J6.R2 (TD-), R31.2; also elsewhere on the board
TX3_ISO_P: J6.R1 (TD+), R30.2; also elsewhere on the board

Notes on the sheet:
FILTERING
POWER SUPLLY AND FILTERING
ETHERNET 3

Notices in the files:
parts and their libraries:
COPYRIGHT: Copyright (C) 2015 Accelerated Designs. All rights reserved
